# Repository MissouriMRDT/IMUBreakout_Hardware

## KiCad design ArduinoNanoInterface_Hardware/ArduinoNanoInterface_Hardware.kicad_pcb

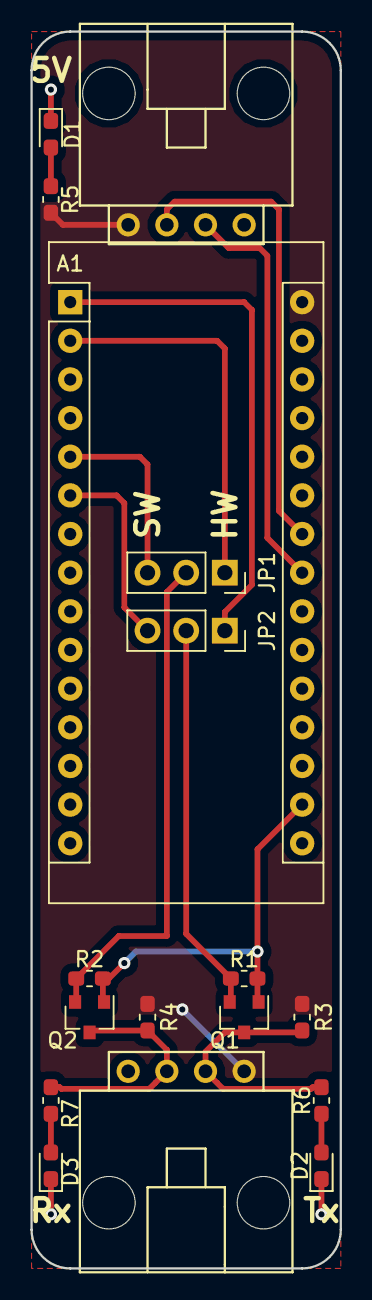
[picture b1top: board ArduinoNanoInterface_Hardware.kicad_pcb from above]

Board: 2 copper layers, 20.3 x 81.3 mm, 17 parts (0 on the bottom side), 16 nets.

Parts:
A1: Arduino_Nano_v3.x; Arduino_Nano
Conn1, Conn2: Molex_SL_04; MOLEX_SL_04_Horizontal
D1, D2, D3: LED; LED_0603_1608Metric_Pad1.05x0.95mm_HandSolder
JP1, JP2: Jumper_NC_Dual; PinSocket_1x03_P2.54mm_Vertical
Q1, Q2: BSS138; SOT-23
R1, R2, R3, R4: 10K; R_0603_1608Metric_Pad1.05x0.95mm_HandSolder
R5, R6, R7: 500; R_0603_1608Metric_Pad1.05x0.95mm_HandSolder

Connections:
+3V3: A1.17, Q1.1, Q2.1, R1.1, R2.1
+5V: A1.30, Conn1.1, Conn2.1, R3.1, R4.1, R5.1
GND: A1.4, A1.29, Conn1.4, Conn2.4, D1.1, D2.1, D3.1
HW_Rx: A1.2, JP1.1
HW_Tx: A1.1, JP2.1
NanoRx: JP1.2, Q2.2, R2.2
NanoTx: JP2.2, Q1.2, R1.2
unnamed: D1.2, R5.2
unnamed: D2.2, R6.2
unnamed: D3.2, R7.2
Rx: Conn2.3, Q2.3, R4.2, R7.1
SCL: A1.24, Conn1.2
SDA: A1.23, Conn1.3
SW_Rx: A1.5, JP1.3
SW_Tx: A1.6, JP2.3
Tx: Conn2.2, Q1.3, R3.2, R6.1

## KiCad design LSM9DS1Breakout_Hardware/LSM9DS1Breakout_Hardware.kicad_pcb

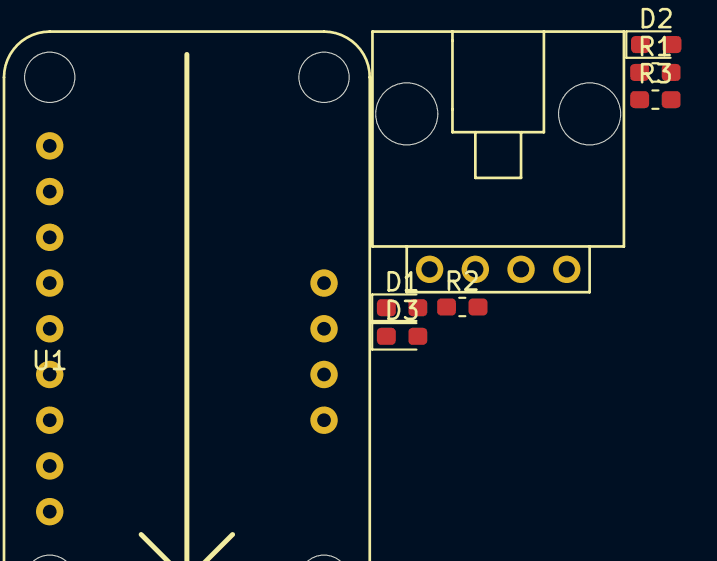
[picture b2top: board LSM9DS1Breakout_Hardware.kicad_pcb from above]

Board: 2 copper layers, 8 parts (0 on the bottom side), 7 nets, no tracks yet.

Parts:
Conn1: Molex_SL_04; MOLEX_SL_04_Horizontal
D1, D2, D3: LED; LED_0603_1608Metric_Pad1.05x0.95mm_HandSolder
R1, R2, R3: 500; R_0603_1608Metric_Pad1.05x0.95mm_HandSolder
U1: Adafruit_LSM9DS1

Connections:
+5V: Conn1.1, R3.1, U1.1
GND: Conn1.4, D1.1, D2.1, D3.1, U1.3
unnamed: D1.2, R1.2
unnamed: D2.2, R2.2
unnamed: D3.2, R3.2
SCL: Conn1.2, R2.1, U1.4
SDA: Conn1.3, R1.1, U1.5

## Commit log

2018-10-10 BreakOutBoard
2018-10-11 Added gitignore
2018-10-11 Added ToDo
2018-10-21 Did everything
2018-12-16 File restructure and created gerbs
2018-12-18 Created Sparkfun Breakout
2019-02-23 Schematic and PCB created
    Rough outlines of board
2019-02-23 SilkScreens
2019-02-27 Added notes
2019-02-28 Changed Board based on Andrew's notes
2019-03-02 created new part
2019-03-02 PCB Finalzied and Made
2019-03-02 addded filled space on PCB
2019-03-03 Fixed PCB, added BOM
2019-03-03 Expand board, Power LED
2019-03-03 BOM updated
2019-03-03 Made zSilkscreen edits
2019-03-03 edge cuts
2019-03-03 Edge cuts done
2019-03-03 logos and signature added
2019-03-04 greated gerbs
2019-03-04 fixed outline
2019-03-04 silkscreeens
2019-04-17 created LSM breakout sch
2019-04-17 fixed adafruit LSM9DS1
2019-04-17 did layout
2019-04-17 created nano interface scheamtic
2019-04-17 layout
2019-04-17 created gerbs
2019-04-19 Fixed gerbs
